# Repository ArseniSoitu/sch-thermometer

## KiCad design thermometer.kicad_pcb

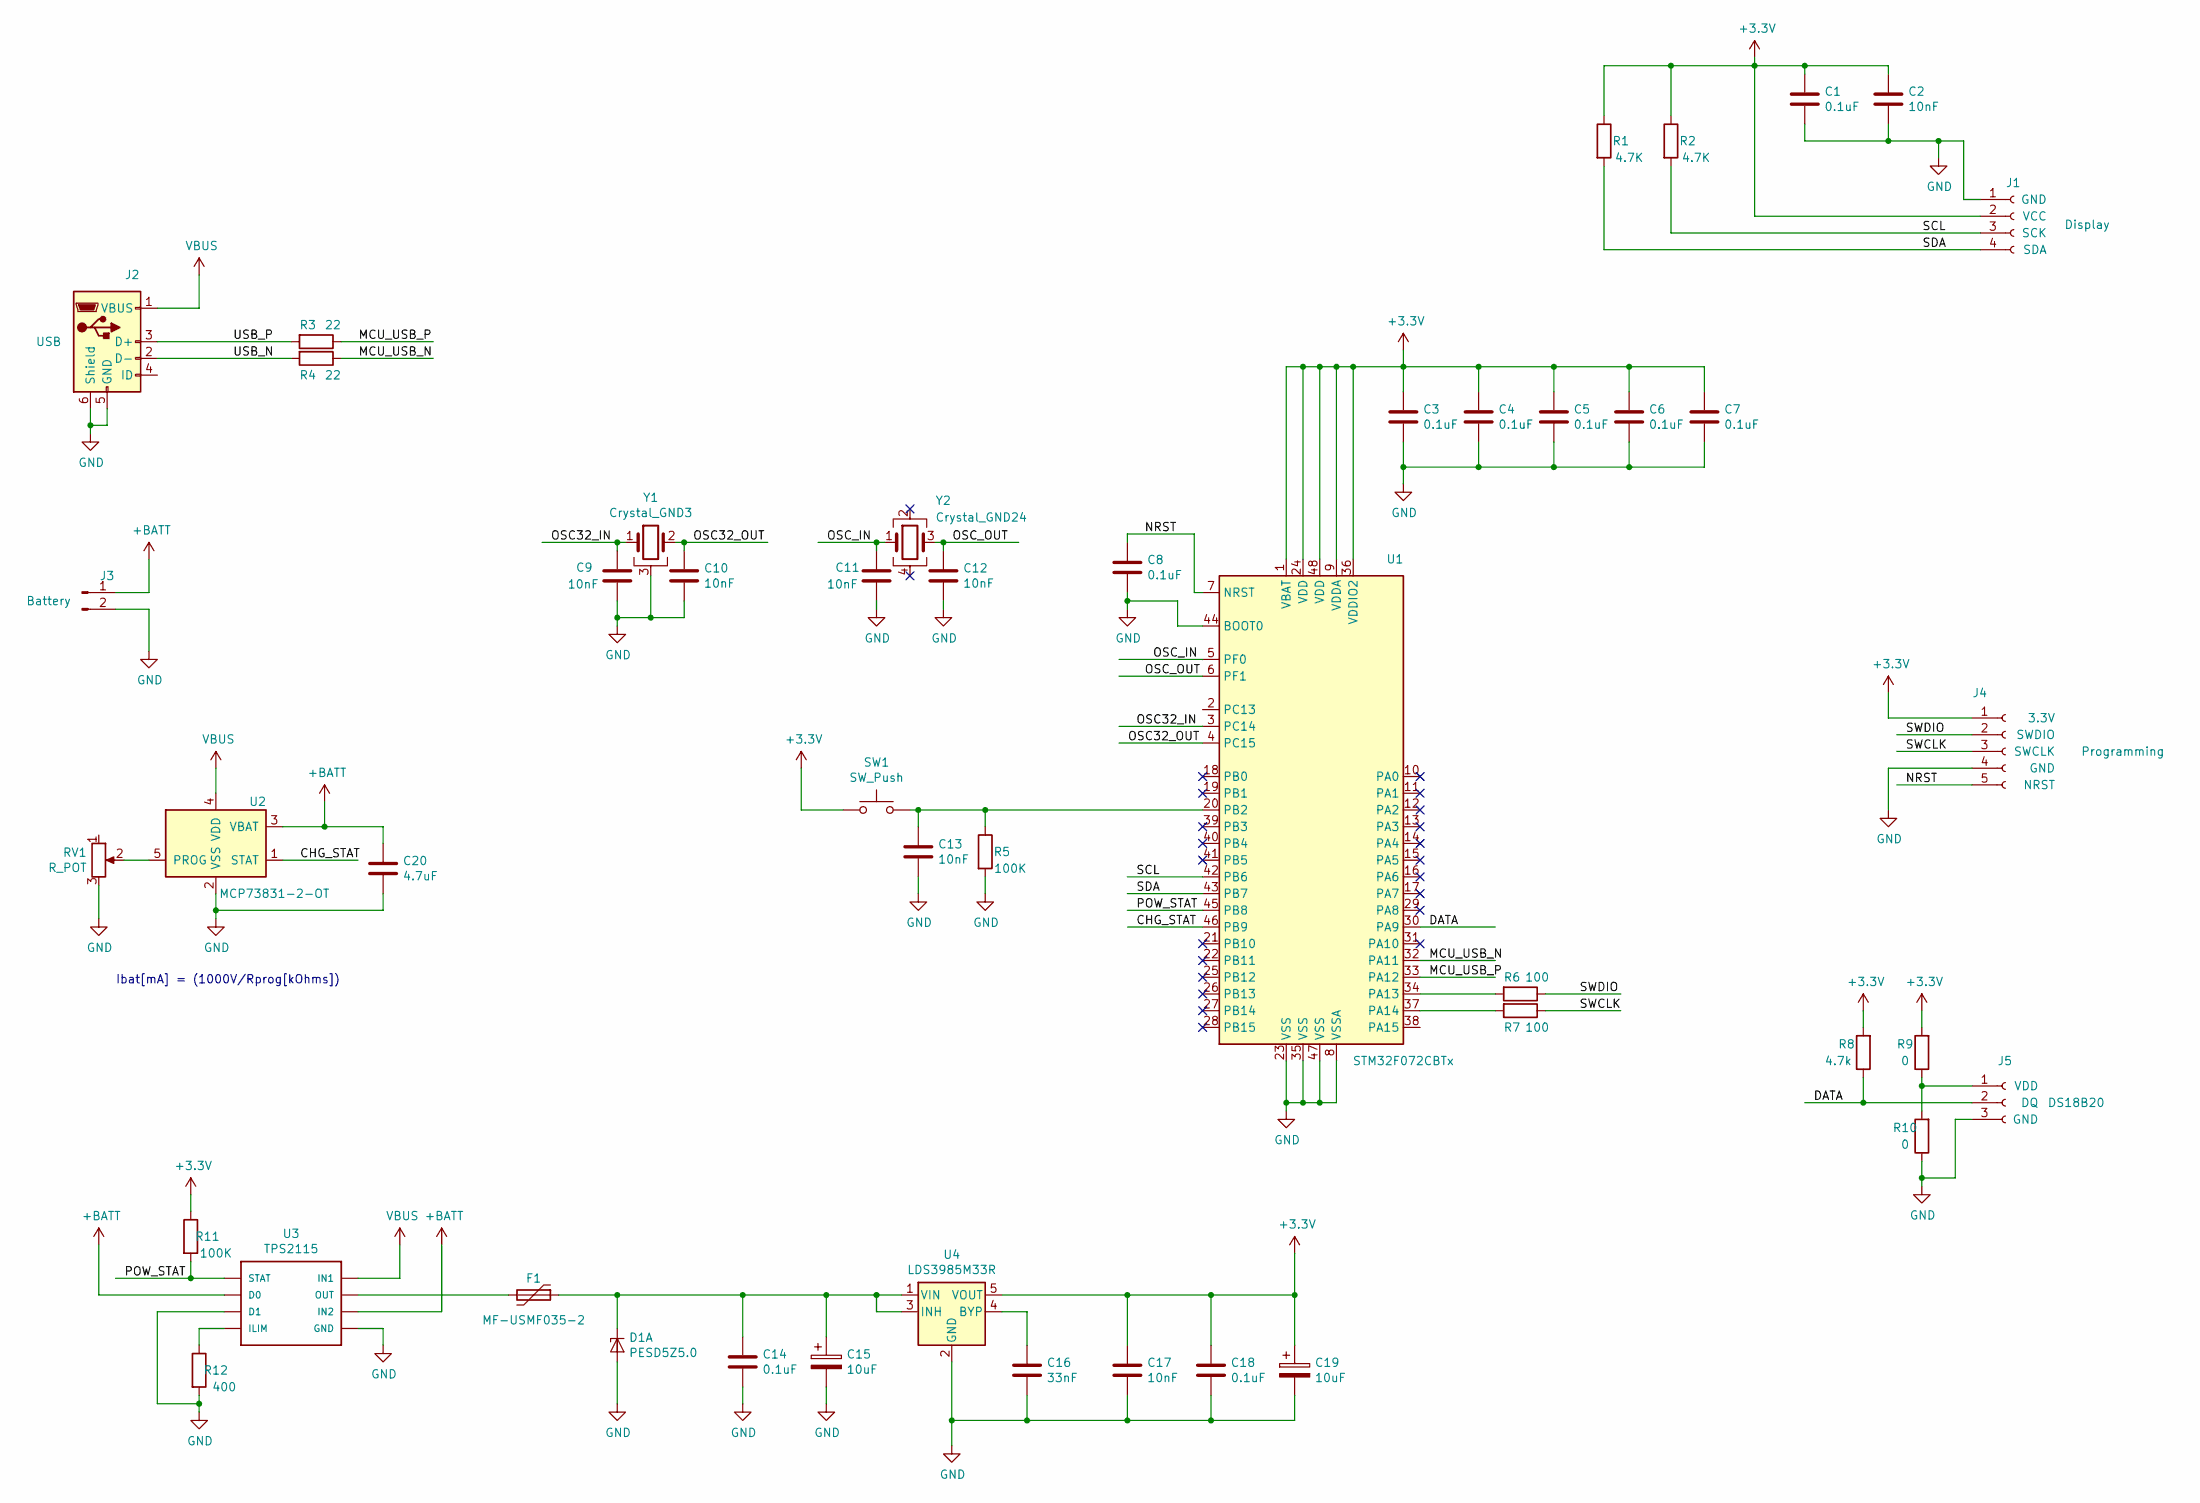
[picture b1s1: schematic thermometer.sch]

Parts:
C1, C3, C4, C5, C6, C7, C8, C14, C18: 0.1uF; C_0603_1608Metric_Pad1.05x0.95mm_HandSolder
C2, C9, C10, C11, C12, C13, C17: 10nF; C_0603_1608Metric_Pad1.05x0.95mm_HandSolder
C15, C19: 10uF; C_0805_2012Metric_Pad1.15x1.40mm_HandSolder
C16: 33nF; C_0603_1608Metric_Pad1.05x0.95mm_HandSolder
C20: 4.7uF; C_0603_1608Metric_Pad1.05x0.95mm_HandSolder
D1: PESD5Z5.0; D_SOD-523
F1: MF-USMF035-2; MF-USMF
J1: Display; PinHeader_1x04_P2.54mm_Vertical
J2: USB; USB_Micro-B_Molex_47346-0001
J3: Battery; SolderWirePad_1x02_P5.08mm_Drill1.5mm
J4: Programming; PinHeader_1x05_P2.54mm_Vertical
J5: DS18B20; JST_PH_S3B-PH-SM4-TB_1x03-1MP_P2.00mm_Horizontal
R1, R2: 4.7K; R_0603_1608Metric_Pad1.05x0.95mm_HandSolder
R3, R4: 22; R_0603_1608Metric_Pad1.05x0.95mm_HandSolder
R5, R11: 100K; R_0603_1608Metric_Pad1.05x0.95mm_HandSolder
R6, R7: 100; R_0603_1608Metric_Pad1.05x0.95mm_HandSolder
R8: 4.7k; R_0603_1608Metric_Pad1.05x0.95mm_HandSolder
R9, R10: 0; R_0603_1608Metric_Pad1.05x0.95mm_HandSolder
R12: 400; R_0603_1608Metric_Pad1.05x0.95mm_HandSolder
RV1: R_POT; Potentiometer_Bourns_3214W_Vertical
SW1: SW_Push; main_button
U1: STM32F072CBTx; LQFP-48_7x7mm_P0.5mm
U2: MCP73831-2-OT; SOT-23-5
U3: TPS2115; TSSOP-8_4.4x3mm_P0.65mm
U4: LDS3985M33R; SOT-23-5
Y1: Crystal_GND3; Crystal_AT310_D3.0mm_L10.0mm_Horizontal_1EP_style1
Y2: Crystal_GND24; Crystal_SMD_3225-4Pin_3.2x2.5mm_HandSoldering

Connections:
+3V3: C1.1, C2.1, C3.1, C4.1, C5.1, C6.1, C7.1, C17.1, C18.1, C19.1, J1.2, J4.1, R1.1, R2.1, R8.2, R9.2, R11.1, SW1.1, U1.1 (VBAT), U1.9 (VDDA), U1.24 (VDD), U1.36 (VDDIO2), U1.48 (VDD), U4.5 (VOUT)
+BATT: C20.1, J3.1, U2.3 (VBAT), U3.2 (D0), U3.6 (IN2)
/CHG_STAT: U1.46 (PB9), U2.1 (STAT)
/DATA: J5.2, R8.1, U1.30 (PA9)
/MCU_USB_N: R4.1, U1.32 (PA11)
/MCU_USB_P: R3.1, U1.33 (PA12)
/NRST: C8.1, J4.5, U1.7 (NRST)
/OSC32_IN: C9.1, U1.3 (PC14), Y1.1
/OSC32_OUT: C10.1, U1.4 (PC15), Y1.2
/OSC_IN: C11.1, U1.5 (PF0), Y2.1
/OSC_OUT: C12.1, U1.6 (PF1), Y2.3
/POW_STAT: R11.2, U1.45 (PB8), U3.1 (STAT)
/SCL: J1.3, R2.2, U1.42 (PB6)
/SDA: J1.4, R1.2, U1.43 (PB7)
/SWCLK: J4.3, R7.1
/SWDIO: J4.2, R6.1
/USB_N: J2.2 (D-), R4.2
/USB_P: J2.3 (D+), R3.2
GND: C1.2, C2.2, C3.2, C4.2, C5.2, C6.2, C7.2, C8.2, C9.2, C10.2, C11.2, C12.2, C13.2, C14.2, C15.2, C16.2, C17.2, C18.2, C19.2, C20.2, D1.2 (A), D1.5 (A), J1.1, J2.5 (GND), J2.6 (Shield), J3.2, J4.4, J5.3, R5.2, R10.1, R12.2, RV1.3, U1.8 (VSSA), U1.23 (VSS), U1.35 (VSS), U1.44 (BOOT0), U1.47 (VSS), U2.2 (VSS), U3.3 (D1), U3.5 (GND), U4.2 (GND), Y1.3
unnamed: C13.1, R5.1, SW1.2, U1.20 (PB2)
unnamed: C14.1, C15.1, D1.1 (K1), F1.1, U4.1 (VIN), U4.3 (INH)
unnamed: C16.1, U4.4 (BYP)
unnamed: F1.2, U3.7 (OUT)
unnamed: J5.1, R9.1, R10.2
unnamed: R6.2, U1.34 (PA13)
unnamed: R7.2, U1.37 (PA14)
unnamed: R12.1, U3.4 (ILIM)
unnamed: RV1.2, U2.5 (PROG)
VBUS: J2.1 (VBUS), U2.4 (VDD), U3.8 (IN1)

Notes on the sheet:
Ibat[mA] = (1000V/Rprog[kOhms])

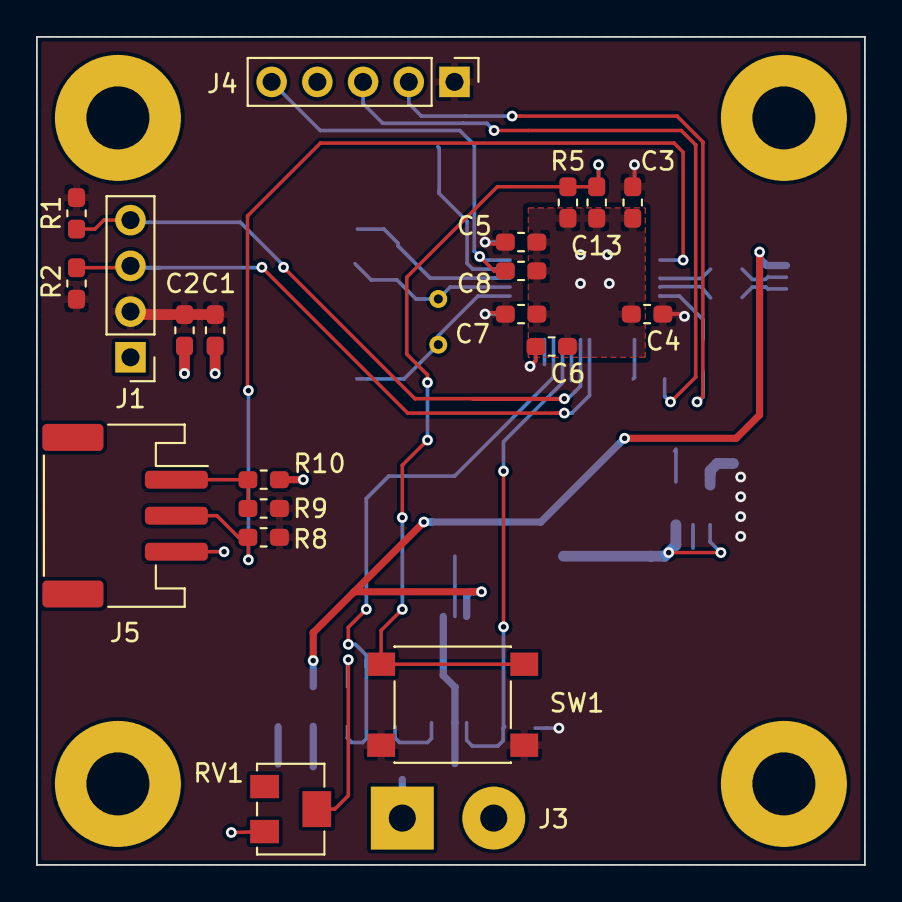
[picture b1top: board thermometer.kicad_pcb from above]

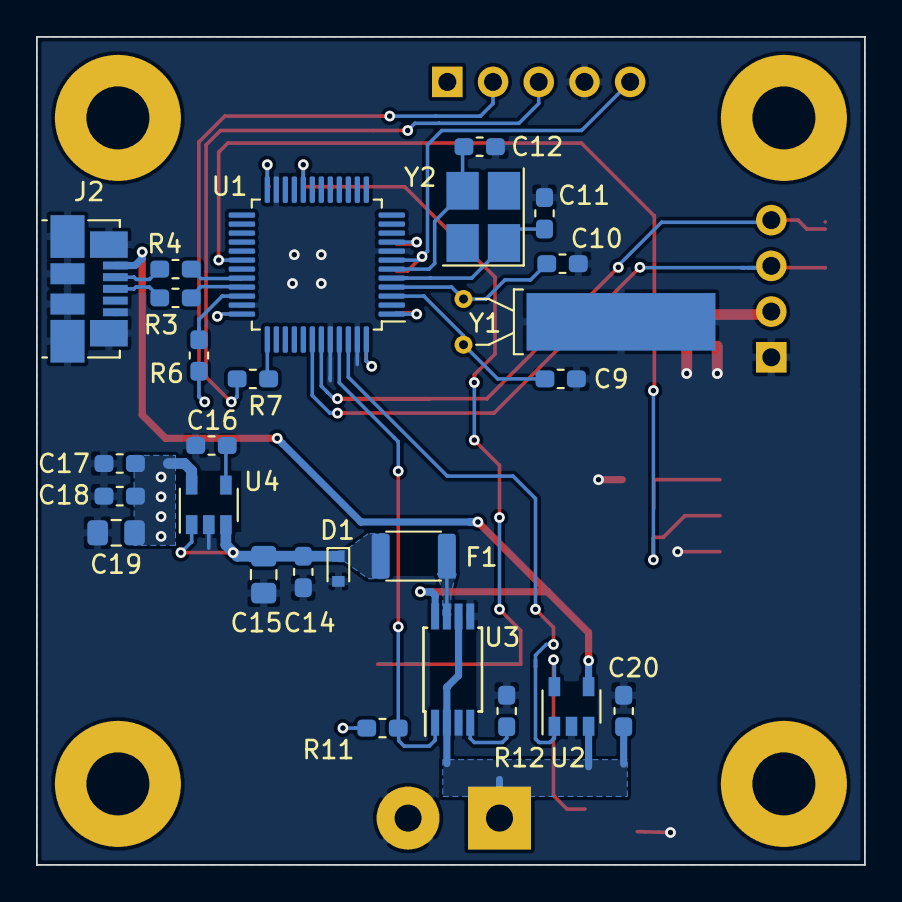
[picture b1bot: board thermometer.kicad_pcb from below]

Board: 2 copper layers, 46.0 x 46.0 mm, 48 parts (26 on the bottom side), 29 nets.

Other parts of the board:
e: MountingHole_3.5mm_Pad

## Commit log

2019-09-07 Finished board
2019-09-07 Added cached lib
2019-09-08 Fixed positions of some elements
2019-09-08 Changed button and dcdc placements
